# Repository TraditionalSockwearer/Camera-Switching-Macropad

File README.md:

# Custom OBS Macropad (RP2040)

## Project Status: Completed

## Project Overview
This project is an ongoing engineering initiative to build a custom, 4-key mechanical macropad designed specifically for **Live OBS (Open Broadcaster Software) Scene Switching**.

**The Use Case:**
This device is being built for a local temple's media team. The goal is to provide volunteer operators with a simplified, fail-safe hardware interface to switch camera angles during live services, eliminating the need to interact with complex software UI during a broadcast.

## Planned Features
* **Context-Aware Display:** Integrated **0.91" OLED** to display active camera scenes ("Camera 1 Active", etc.).
* **Synced RGB Feedback:** 4x **SK6812 Mini-E LEDs** that provide colour-coded status indicators synchronised with the active scene.
* **USB HID Interface:** Acts as a standard keyboard sending F13-F16 keys to trigger OBS hotkeys.
* **Compact Form Factor:** Custom 3D-printed enclosure with heat-set inserts for durability.

## Tech Stack
* **Microcontroller:** Seeed Studio XIAO RP2040
* **EDA / PCB:** KiCad 9
* **CAD:** Fusion 360
* **Firmware:** Python (MicroPython) with State Machine logic.
* **Simulation:** Wokwi (Used to validate I2C OLED & NeoPixel logic) and onboard testing.

## Development Roadmap
- [x] **Requirement Analysis:** Defined constraints (silent switches, OLED feedback).
- [x] **Component Sourcing:** Validated BOM (Bill of Materials) for cost/availability.
- [x] **Schematic Capture:** Completed electrical schematic in KiCad.
- [x] **PCB Layout:** Routing tracks and defining edge cuts (In Progress).
- [x] **Prototyping:** 3D printing the case and soldering the first unit.
- [x] **Firmware Prototype:** Created state-machine logic in Wokwi (Simulation).
- [x] **Integration:** Final HID implementation and OBS setup at the venue.

## Repository Structure
```text
/CAD          # STL files (In Progress)
/PCB       # Schematic and PCB files
/Firmware     # Wokwi simulation code and future main.py
```

## CAD Model

Made in Fusion360

## PCB

## Schematic

# BOM

* 4x Cherry MX Switches 

* 2x SK6812 MINI Leds

SK6812 MINI-E RGB 20PCS Link: 

    https://www.aliexpress.com/item/1005008308801366.html

* 1x XIAO RP2040 

Seeed XIAO RP2040 Link: 

    https://www.aliexpress.com/item/1005008200917480.html

* 4x Blank DSA Keycaps

Blank Keycaps 10PCS Link: 
    
    https://www.aliexpress.com/item/1005005514406952.html

* 4x M3x16 Bolt 

M3x16mm Screw Link: 
    
    https://www.aliexpress.com/item/1005008585550992.html

* 4x M3 Heatset 

M3 Heat Set Link: 

    https://www.aliexpress.com/item/1005008897571758.html

* 1x 0.91" 128x32 OLED Display 

OLED Display Link: 

    https://www.aliexpress.com/item/1005008640108394.html

* 1x Case (2 parts: Bottom Case and Cover)

* 1x PCB

I used JLBPCB for PCB
Gerber files are made by opening pcb file. Then press the Files, then Plot, and make sure to press drill and as a single file (it's an option)

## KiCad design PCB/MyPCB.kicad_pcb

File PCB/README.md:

# Requires Footprint
It is in .gitmodules. However, it doesn't upload so u need to add
Oled display

    https://github.com/gorbachev/KiCad-SSD1306-0.91-OLED-4pin-128x32.pretty/tree/master

Switches

    https://github.com/ai03-2725/MX_V2

OPL_Kicad_Libary

    https://github.com/Seeed-Studio/OPL_Kicad_Library

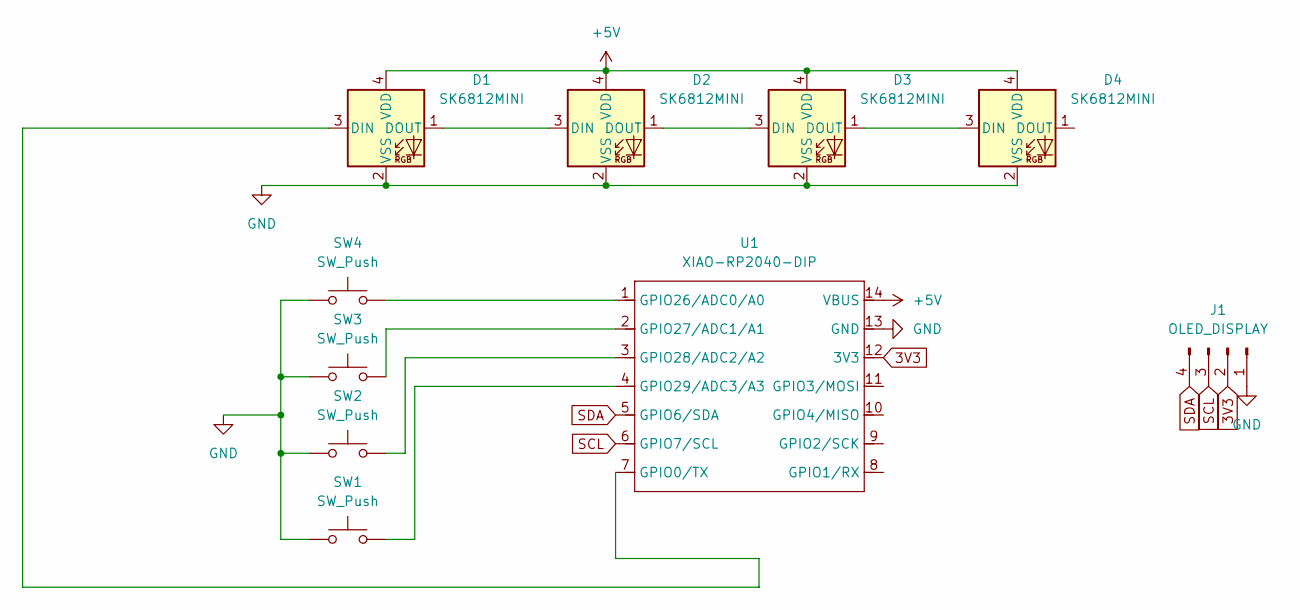
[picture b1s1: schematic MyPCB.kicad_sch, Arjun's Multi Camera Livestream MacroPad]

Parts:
D1, D2, D3, D4: SK6812MINI; LED_SK6812MINI_PLCC4_3.5x3.5mm_P1.75mm
J1: OLED_DISPLAY; SSD1306-0.91-OLED-4pin-128x32
SW1, SW2, SW3, SW4: SW_Push; SW_Cherry_MX_1.00u_PCB
U1: XIAO-RP2040-DIP

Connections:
3V3: J1.2, U1.12 (3V3)
+5V: D1.4 (VDD), D2.4 (VDD), D3.4 (VDD), D4.4 (VDD), U1.14 (VBUS)
GND: D1.2 (VSS), D2.2 (VSS), D3.2 (VSS), D4.2 (VSS), J1.1, SW1.1, SW2.1, SW3.1, SW4.1, U1.13 (GND)
unnamed: D1.3 (DIN), U1.7 (GPIO0/TX)
unnamed: D1.1 (DOUT), D2.3 (DIN)
unnamed: D2.1 (DOUT), D3.3 (DIN)
unnamed: D3.1 (DOUT), D4.3 (DIN)
unnamed: SW4.2, U1.1 (GPIO26/ADC0/A0)
unnamed: SW3.2, U1.2 (GPIO27/ADC1/A1)
unnamed: SW2.2, U1.3 (GPIO28/ADC2/A2)
unnamed: SW1.2, U1.4 (GPIO29/ADC3/A3)
SCL: J1.3, U1.6 (GPIO7/SCL)
SDA: J1.4, U1.5 (GPIO6/SDA)

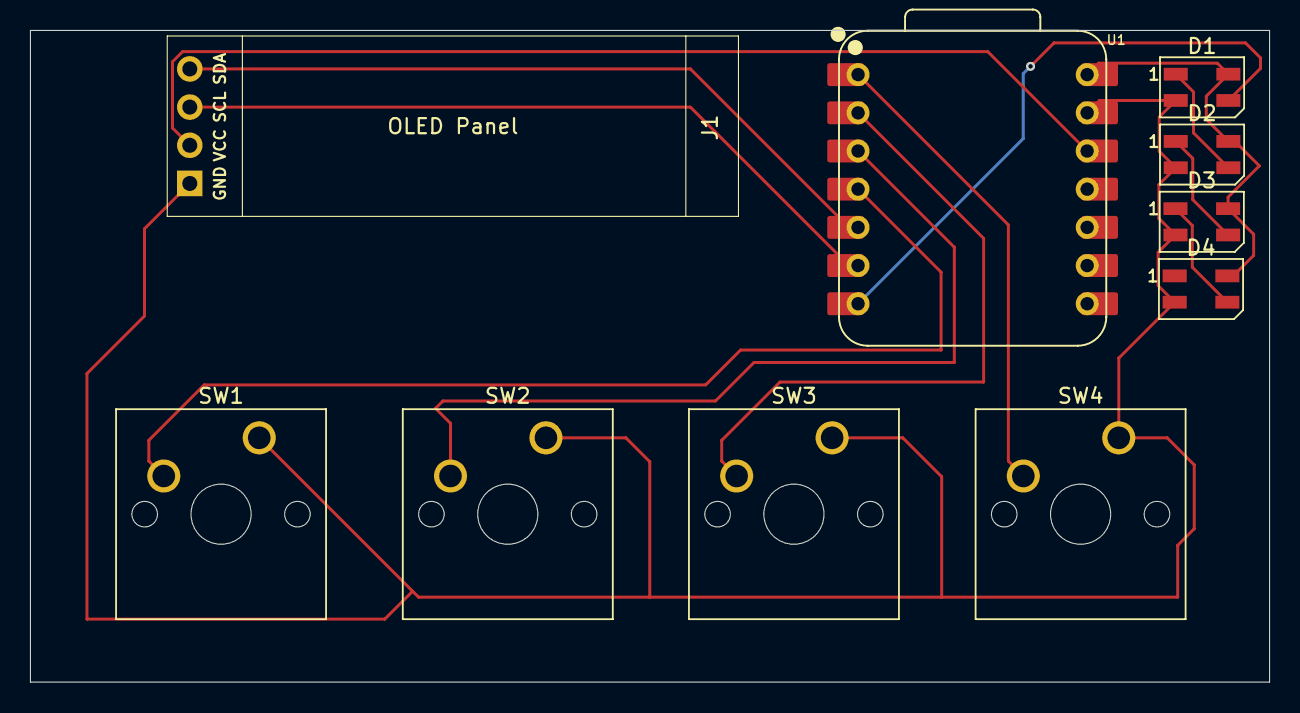
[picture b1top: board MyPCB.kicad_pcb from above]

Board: 2 copper layers, 82.4 x 43.3 mm, 10 parts (0 on the bottom side), 13 nets.

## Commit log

2025-11-29 Update PCB Design
2025-11-29 Cool thing
2025-11-30 Finished PCB
2025-11-30 Finished commiting
    done
2025-11-30 Fixing
2025-11-30 Fix part 2
2025-12-01 Started main firmware without module
2025-12-03 finish case
2025-12-04 Create LICENSE
2025-12-04 Sorting Directories and adding .step files
2025-12-17 First Revision of code
    Keys are fully functioning will need changing on second revision animation works and screen works. LED are not working and libraries for them haven't been uploaded
2025-12-17 Firmware Revision 2
2025-12-17 Create README.md for firmware
2026-01-29 Add layer switching and media controls to keyboard
    Introduced Layers and HoldTap modules to support multiple keyboard layers (Menu, OBS, Media) and added media key handling with display feedback. Updated keymap and handlers for switching modes, media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
2026-01-30 feat: Add core CircuitPython libraries, KMK firmware components, and project-specific modules.
2026-01-30 Update kmk_firmware submodule to latest commit
    Advanced the kmk_firmware submodule from commit 5a6669d to 63d1046 to incorporate upstream changes and improvements.
2026-01-30 Re adding pcb and cad for merge
2026-01-30 Strictly Making it firmware only
2026-01-30 Move Gerber files to PCB/Gerber and clean backups
    Relocated all Gerber and related output files from PCB/ to PCB/Gerber for better organization. Removed old backup ZIP files and a KiCad lock file to clean up the repository.
2026-01-30 Update project status to 'Completed' in README
2026-01-30 Change project status to 'Completed'
    Updated project status to 'Completed' and removed details about active development phase.
2026-01-30 Android Compatability Test 1
2026-01-30 Enhance Android media bridge with termux-usb support
    Refactor the script to support running via termux-usb, allowing USB device path to be passed as an argument for permission handling. Add device listing, permission request, and improved user guidance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
